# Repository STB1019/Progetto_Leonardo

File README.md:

<br/>
<p align="center">
  <h1 align="center">Progetto Leonardo</h1>

  <p align="center">
    An IEEE Student Branch Project
    <br/>
    <br/>
  </p>
</p>

<!--    
-->
## Table Of Contents

* [About the Project](#about-the-project)
* [Built With](#built-with)
* [Roadmap](#roadmap)
* [Authors](#authors)

## About The Project

Project with the aim of building a robot that is able to move and climb stairs.

## Built With

Raspberry and Arduino

## Roadmap

See the [open issues](https://github.com/TTT357C/Progetto_Leonardo/issues) for a list of proposed features (and known issues). </br>
See also our trello [Trello](https://trello.com/b/dbFiTYEp/progetto-leonardo-ieee-student-branch-brescia)

## Authors

* **Thomas Causetti** - *Engineering Student and Member of IEEE* - [Thomas Causetti](https://github.com/TTT357C/) - *Programmer and Designer*
* **Mirko Rossi** - *Engineering Student and Member of IEEE* - [Mirko Rossi](https://github.com/Zphyr19) - *Programmer*
* **Abdel** - *Engineering Student and Member of IEEE* - [Abdel](https://github.com/99Abdel) - *Programmer*
* **Stefano Molari** - *Engineering Student and Member of IEEE* - [Stefano Molari](https://github.com/steMola) - *Circuit Designer*

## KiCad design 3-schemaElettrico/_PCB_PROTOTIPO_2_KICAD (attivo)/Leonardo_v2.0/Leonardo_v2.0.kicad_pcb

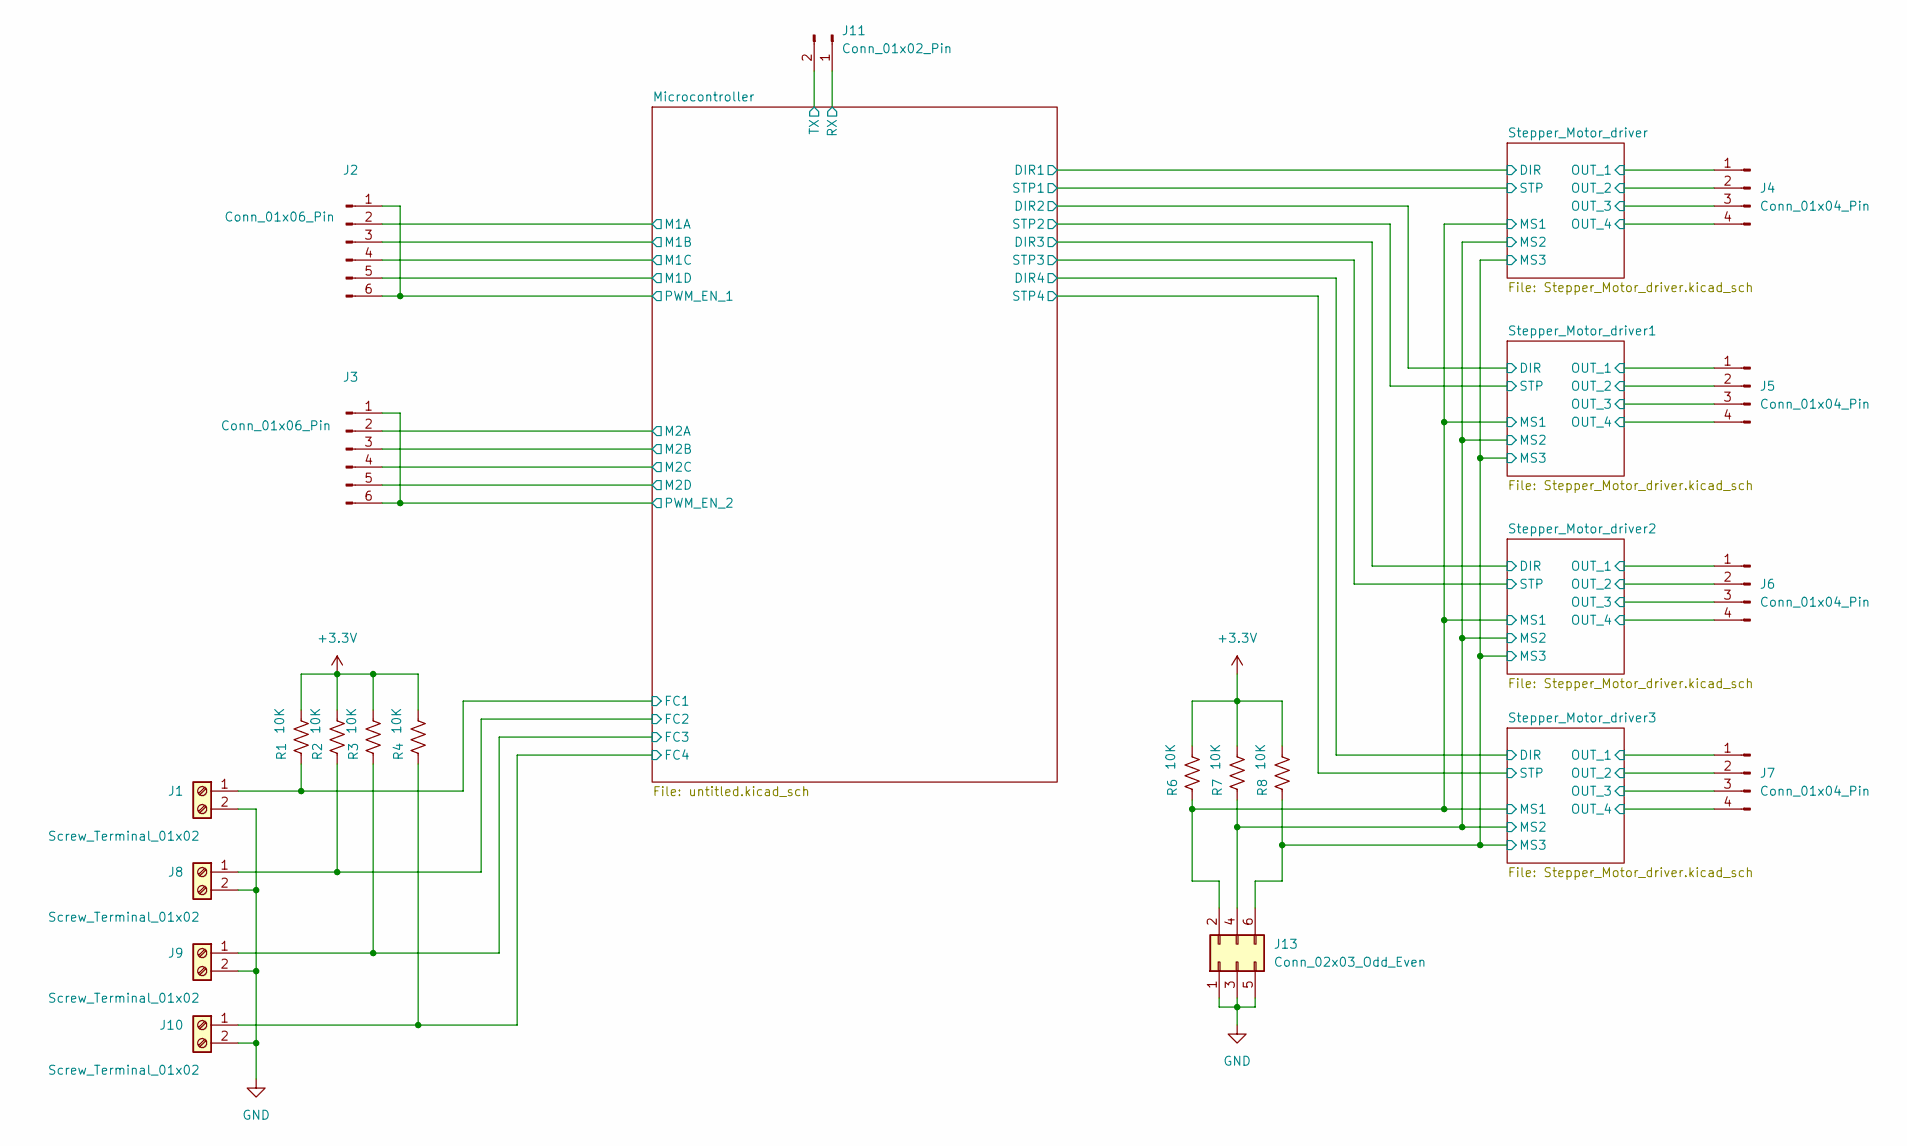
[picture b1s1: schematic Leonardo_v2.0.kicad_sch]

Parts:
J1, J8, J9, J10: Screw_Terminal_01x02; TerminalBlock_Phoenix_MKDS-1,5-2_1x02_P5.00mm_Horizontal
J2, J3: Conn_01x06_Pin; PinHeader_1x06_P2.54mm_Vertical
J4, J5, J6, J7: Conn_01x04_Pin; PinHeader_1x04_P2.54mm_Vertical
J11: Conn_01x02_Pin
J13: Conn_02x03_Odd_Even; PinHeader_2x03_P2.54mm_Vertical
R1, R2, R3, R4, R6, R7, R8: 10K; R_0805_2012Metric

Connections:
+3.3V: R1.2, R2.2, R3.2, R4.2, R6.2, R7.2, R8.2; also elsewhere on the board
/Microcontroller/FC1: J1.1, R1.1; also elsewhere on the board
/Microcontroller/FC2: J8.1, R2.1; also elsewhere on the board
/Microcontroller/FC3: J9.1, R3.1; also elsewhere on the board
/Microcontroller/FC4: J10.1, R4.1; also elsewhere on the board
/Microcontroller/M1A: J2.2; also elsewhere on the board
/Microcontroller/M1B: J2.3; also elsewhere on the board
/Microcontroller/M1C: J2.4; also elsewhere on the board
/Microcontroller/M1D: J2.5; also elsewhere on the board
/Microcontroller/M2A: J3.2; also elsewhere on the board
/Microcontroller/M2B: J3.3; also elsewhere on the board
/Microcontroller/M2C: J3.4; also elsewhere on the board
/Microcontroller/M2D: J3.5; also elsewhere on the board
/Microcontroller/PWM_EN_1: J2.1, J2.6; also elsewhere on the board
/Microcontroller/PWM_EN_2: J3.1, J3.6; also elsewhere on the board
/Stepper_Motor_driver1/OUT_1: J5.1; also elsewhere on the board
/Stepper_Motor_driver1/OUT_2: J5.2; also elsewhere on the board
/Stepper_Motor_driver1/OUT_3: J5.3; also elsewhere on the board
/Stepper_Motor_driver1/OUT_4: J5.4; also elsewhere on the board
/Stepper_Motor_driver2/OUT_1: J6.1; also elsewhere on the board
/Stepper_Motor_driver2/OUT_2: J6.2; also elsewhere on the board
/Stepper_Motor_driver2/OUT_3: J6.3; also elsewhere on the board
/Stepper_Motor_driver2/OUT_4: J6.4; also elsewhere on the board
/Stepper_Motor_driver3/OUT_1: J7.1; also elsewhere on the board
/Stepper_Motor_driver3/OUT_2: J7.2; also elsewhere on the board
/Stepper_Motor_driver3/OUT_3: J7.3; also elsewhere on the board
/Stepper_Motor_driver3/OUT_4: J7.4; also elsewhere on the board
/Stepper_Motor_driver/MS1: J13.2, R6.1; also elsewhere on the board
/Stepper_Motor_driver/MS2: J13.4, R7.1; also elsewhere on the board
/Stepper_Motor_driver/MS3: J13.6, R8.1; also elsewhere on the board
/Stepper_Motor_driver/OUT_1: J4.1; also elsewhere on the board
/Stepper_Motor_driver/OUT_2: J4.2; also elsewhere on the board
/Stepper_Motor_driver/OUT_3: J4.3; also elsewhere on the board
/Stepper_Motor_driver/OUT_4: J4.4; also elsewhere on the board
GND: J1.2, J8.2, J9.2, J10.2, J13.1, J13.3, J13.5; also elsewhere on the board

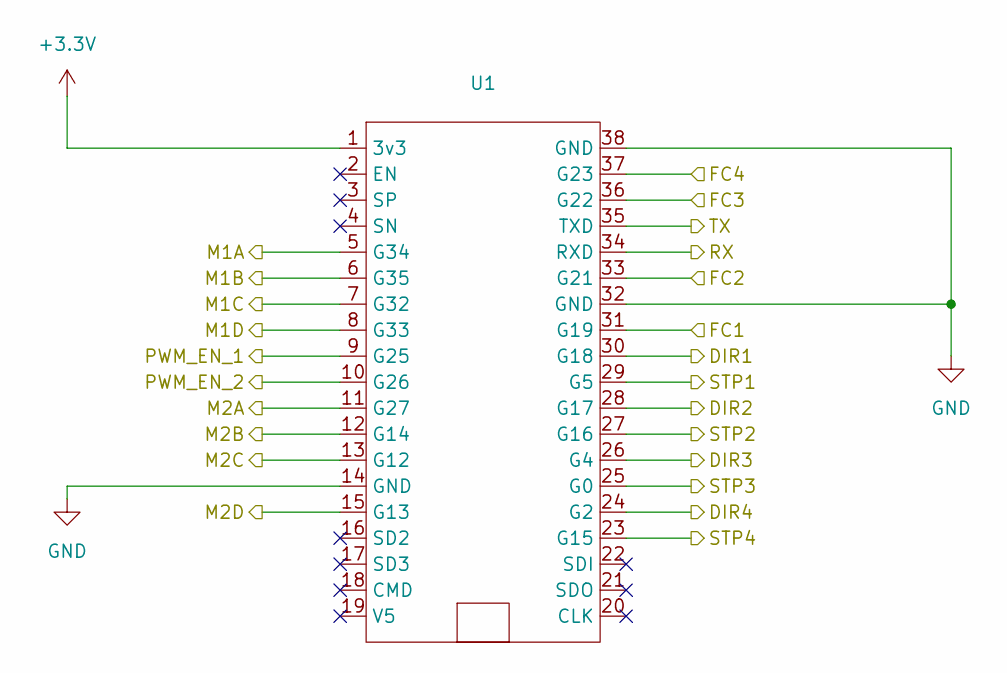
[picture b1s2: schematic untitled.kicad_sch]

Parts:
U1: DIP-38_1000_ELL

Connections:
+3.3V: U1.1 (3v3); also elsewhere on the board
/Microcontroller/DIR1: U1.29 (G5); also elsewhere on the board
/Microcontroller/DIR2: U1.27 (G16); also elsewhere on the board
/Microcontroller/DIR3: U1.25 (G0); also elsewhere on the board
/Microcontroller/DIR4: U1.23 (G15); also elsewhere on the board
/Microcontroller/FC1: U1.31 (G19); also elsewhere on the board
/Microcontroller/FC2: U1.33 (G21); also elsewhere on the board
/Microcontroller/FC3: U1.36 (G22); also elsewhere on the board
/Microcontroller/FC4: U1.37 (G23); also elsewhere on the board
/Microcontroller/M1A: U1.5 (G34); also elsewhere on the board
/Microcontroller/M1B: U1.6 (G35); also elsewhere on the board
/Microcontroller/M1C: U1.7 (G32); also elsewhere on the board
/Microcontroller/M1D: U1.8 (G33); also elsewhere on the board
/Microcontroller/M2A: U1.11 (G27); also elsewhere on the board
/Microcontroller/M2B: U1.12 (G14); also elsewhere on the board
/Microcontroller/M2C: U1.13 (G12); also elsewhere on the board
/Microcontroller/M2D: U1.15 (G13); also elsewhere on the board
/Microcontroller/PWM_EN_1: U1.9 (G25); also elsewhere on the board
/Microcontroller/PWM_EN_2: U1.10 (G26); also elsewhere on the board
/Microcontroller/RX: U1.34 (RXD)
/Microcontroller/STP1: U1.30 (G18); also elsewhere on the board
/Microcontroller/STP2: U1.28 (G17); also elsewhere on the board
/Microcontroller/STP3: U1.26 (G4); also elsewhere on the board
/Microcontroller/STP4: U1.24 (G2); also elsewhere on the board
/Microcontroller/TX: U1.35 (TXD)
GND: U1.14 (GND), U1.32 (GND), U1.38 (GND); also elsewhere on the board

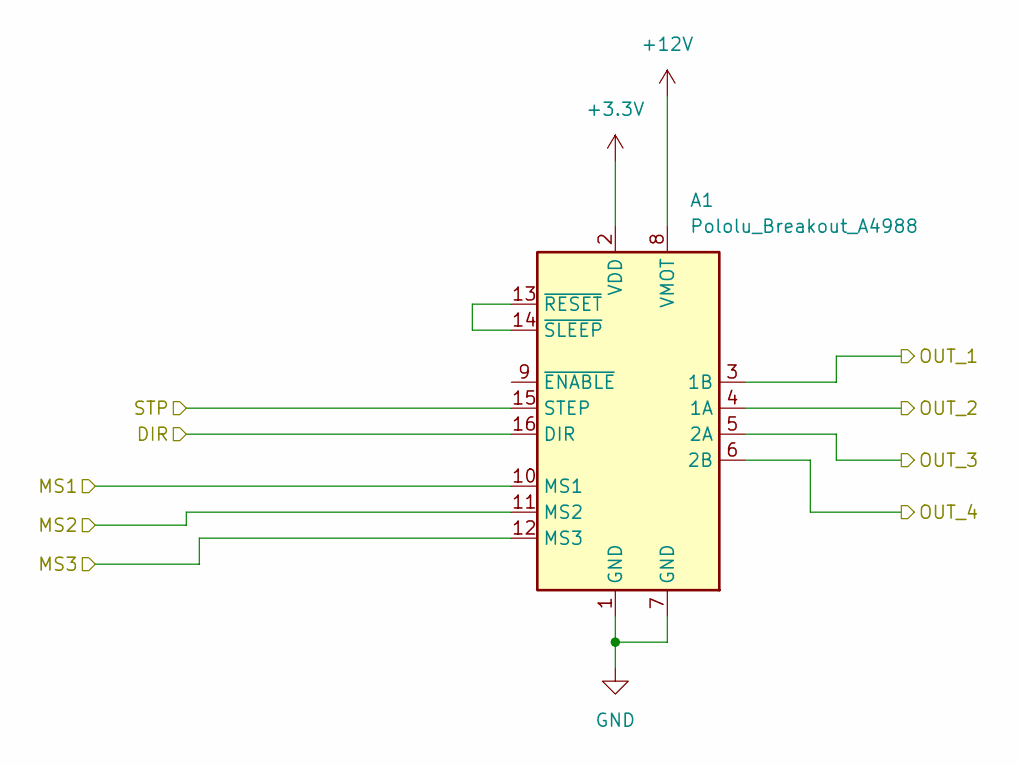
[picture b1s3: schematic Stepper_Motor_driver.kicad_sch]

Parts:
A1: Pololu_Breakout_A4988; Pololu_Breakout-16_15.2x20.3mm

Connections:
+3.3V: A1.2 (VDD); also elsewhere on the board
+12V: A1.8 (VMOT); also elsewhere on the board
/Microcontroller/DIR1: A1.16 (DIR); also elsewhere on the board
/Microcontroller/STP1: A1.15 (STEP); also elsewhere on the board
/Stepper_Motor_driver/MS1: A1.10 (MS1); also elsewhere on the board
/Stepper_Motor_driver/MS2: A1.11 (MS2); also elsewhere on the board
/Stepper_Motor_driver/MS3: A1.12 (MS3); also elsewhere on the board
/Stepper_Motor_driver/OUT_1: A1.3 (1B); also elsewhere on the board
/Stepper_Motor_driver/OUT_2: A1.4 (1A); also elsewhere on the board
/Stepper_Motor_driver/OUT_3: A1.5 (2A); also elsewhere on the board
/Stepper_Motor_driver/OUT_4: A1.6 (2B); also elsewhere on the board
GND: A1.1 (GND), A1.7 (GND); also elsewhere on the board
unnamed: A1.13 (~RESET), A1.14 (~SLEEP)

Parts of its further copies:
A2, A3, A4: Pololu_Breakout_A4988; Pololu_Breakout-16_15.2x20.3mm

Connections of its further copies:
+3.3V: A2.2 (VDD), A3.2 (VDD), A4.2 (VDD); also elsewhere on the board
+12V: A2.8 (VMOT), A3.8 (VMOT), A4.8 (VMOT); also elsewhere on the board
/Microcontroller/DIR2: A2.16 (DIR); also elsewhere on the board
/Microcontroller/DIR3: A3.16 (DIR); also elsewhere on the board
/Microcontroller/DIR4: A4.16 (DIR); also elsewhere on the board
/Microcontroller/STP2: A2.15 (STEP); also elsewhere on the board
/Microcontroller/STP3: A3.15 (STEP); also elsewhere on the board
/Microcontroller/STP4: A4.15 (STEP); also elsewhere on the board
/Stepper_Motor_driver1/OUT_1: A2.3 (1B); also elsewhere on the board
/Stepper_Motor_driver1/OUT_2: A2.4 (1A); also elsewhere on the board
/Stepper_Motor_driver1/OUT_3: A2.5 (2A); also elsewhere on the board
/Stepper_Motor_driver1/OUT_4: A2.6 (2B); also elsewhere on the board
/Stepper_Motor_driver2/OUT_1: A3.3 (1B); also elsewhere on the board
/Stepper_Motor_driver2/OUT_2: A3.4 (1A); also elsewhere on the board
/Stepper_Motor_driver2/OUT_3: A3.5 (2A); also elsewhere on the board
/Stepper_Motor_driver2/OUT_4: A3.6 (2B); also elsewhere on the board
/Stepper_Motor_driver3/OUT_1: A4.3 (1B); also elsewhere on the board
/Stepper_Motor_driver3/OUT_2: A4.4 (1A); also elsewhere on the board
/Stepper_Motor_driver3/OUT_3: A4.5 (2A); also elsewhere on the board
/Stepper_Motor_driver3/OUT_4: A4.6 (2B); also elsewhere on the board
/Stepper_Motor_driver/MS1: A2.10 (MS1), A3.10 (MS1), A4.10 (MS1); also elsewhere on the board
/Stepper_Motor_driver/MS2: A2.11 (MS2), A3.11 (MS2), A4.11 (MS2); also elsewhere on the board
/Stepper_Motor_driver/MS3: A2.12 (MS3), A3.12 (MS3), A4.12 (MS3); also elsewhere on the board
GND: A2.1 (GND), A2.7 (GND), A3.1 (GND), A3.7 (GND), A4.1 (GND), A4.7 (GND); also elsewhere on the board
unnamed: A2.13 (~RESET), A2.14 (~SLEEP)
unnamed: A3.13 (~RESET), A3.14 (~SLEEP)
unnamed: A4.13 (~RESET), A4.14 (~SLEEP)

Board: 2 copper layers, 23 parts (0 on the bottom side), 48 nets, no tracks yet.

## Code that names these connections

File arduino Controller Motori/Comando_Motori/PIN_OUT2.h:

#define dir1 5
#define dir2 6
#define dir3 7
#define dir4 8

#define pwm 9

#define dir_step1 10
#define dir_step2 12
#define dir_step3 14
#define dir_step4 19

#define step1 11
#define step2 13
#define step3 15
#define step4 16

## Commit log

2023-09-27 Upload Onedrive Folder
2023-11-22 Update Notes: Simple Update Version: - Prog: Thomas
2023-11-22 Update Notes: Simple Update Version: 1.1 Prog: Thomas
2023-11-29 Fixed - testing needed
2024-03-01 On branch refactoring
2024-03-01 Changes to be committed:
2024-03-03 Create Sonar_Completo_Leonardo.ino
    Gestione della funzione di sonar del drone.
    Lancio di n scansioni per ogni passo del servo motore.
    Angolo di lavoro di 60 gradi.
    Possibilità di spostare l'angolo di lavoro per una migliore visuale prima di una svolta.
    PS: I pin utilizzati sono stati scelti per semplicità di test durante la scrittura del codice e sono ovviamente modificabili.
2024-03-06 renamed: Comando_finale/1- Arduino/Sonar_Completo_Leonardo.ino -> Comando_finale/1- Arduino/Sonar_Completo_Leonardo.h
2024-03-06 new file: Comando_finale/1- Arduino/MainController/MainController.ino
2024-03-08 Changes to be committed: modified: Comando_finale/1- Arduino/MainController/Movement.h modified: Comando_finale/1- Arduino/MainController/PIN_OUT_FINAL.h modified: Comando_finale/1- Arduino/MainContr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
2024-03-13 modified: Comando_finale/1- Arduino/MainController/MainController.ino modified: Comando_finale/1- Arduino/MainController/PIN_OUT_FINAL.h new file: Comando_finale/1- Arduino/MainController/Stepper2.h
2024-03-13 modified: Comando_finale/1- Arduino/MainController/MainController.ino modified: Comando_finale/1- Arduino/MainController/Movement.h modified: Comando_finale/1- Arduino/MainController/PIN_OUT_FINAL.h 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
2024-04-10 modificato: Comando_finale/1- Arduino/MainController/MainController.ino modificato: Comando_finale/1- Arduino/MainController/Movement.h modificato: Comando_finale/1- Arduino/MainController/Stepper2.h
2024-04-17 modificato: Comando_finale/1- Arduino/MainController/Movement.h
2024-04-17 modificato: Comando_finale/1- Arduino/MainController/MainController.ino modificato: Old_project/TEST motori Molari/TEST_DC/TEST_DC.ino modificato: Old_project/TEST motori Molari/TEST_STEPPER/STEPPER_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
2024-04-24 prototype stepper function for movement automatically directioned
2024-04-24 modified: Comando_finale/1- Arduino/MainController/MainController.ino modified: Comando_finale/1- Arduino/MainController/Movement.h
2024-04-24 modified: Comando_finale/1- Arduino/MainController/MainController.ino modified: Old_project/TEST motori Molari/TEST_STEPPER/STEPPER_A4988/STEPPER_A4988.ino
2024-04-24 Update Notes: Python gui Prog: Thomas
2024-04-24 test commit
2024-04-24 delay with variable
2024-04-24 modified: Comando_finale/1- Arduino/MainController/MainController.ino
2024-04-25 bug fixing function dummyStepper
2024-05-15 fixing pwm function
2024-05-29 proto of the MQTT connection
2024-10-02 refactoring serial comm methods
2024-10-04 serial sowftware refactored
2024-10-09 todo: fixing serial comm
2024-10-10 utile
2024-10-16 todo: use only serialWriter when writing serial messages
2024-11-13 linking serial communication and movement
2024-11-13 aaaaaaaaaa
2024-11-13 serial modifications
2024-12-04 serial modification: finally works
2024-12-06 serial analyzer bitwise version created
2024-12-11 ''merging'' branches
2024-12-11 test for killing stop after every loop
2024-12-11 serial finally works without stopping
2024-12-11 serial implementing start, stop, pwm change and security lock
2024-12-18 testing buffer
2025-03-27 done 74hc238
2025-04-01 placed nodeMCU
2025-04-30 refactoring the code
2025-05-07 minor changes
2025-05-11 serial communication opened with esp32, but only works esp->pc
2025-05-13 semplificato
2025-05-28 ohriqeurbiuqweugfqwrgfwuifher9
2025-05-28 FUNZIONA
2025-10-22 hardware controller software added
2025-11-12 pull
2025-11-26 bug fixing and code lightening
2025-11-26 sonar working finally
2025-11-26 python from raspberry
2025-12-10 skill issue for 1 week commit delay
